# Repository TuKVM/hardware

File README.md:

# TuKVM Hardware

TuKVM is a hardware project that aims to provide a simple but feature rich IP KVM solution. The project is based on the [Tronlong SOM-TLT113](https://www.tronlong.com/Product/show/237.html) SoM, which includes an Allwinner T113-i SoC, with dual-core Cortex-A7 CPU, 256MB DDR3 RAM, and 4GB eMMC.

## Features

* PCIe x1 half-height form factor, with breakable edge connector for mounting in systems without free slots
* HDMI input capture (up to 1080P30) with [MS2109](http://en.macrosilicon.com/info.asp?base_id=2&third_id=50) IC
* ATX power / reset button control with opto-isolator
* Power and HDD LED monitoring with opto-isolator
* 9 pin 2.54mm internal USB OTG port for mass-storage, keyboard, mouse emulation and Ethernet-over-USB
* USB-C external power input and UART console port for debugging
* 100Mbps Ethernet with [LAN8720A](https://www.microchip.com/en-us/product/lan8720a) PHY
* RS232 serial port with 2.54mm header for host system console redirection
* SMBus on PCIe connector for Linux kernel to recongnize the KVM as an IPMI device, using [ipmi_ssif](https://github.com/torvalds/linux/blob/master/drivers/char/ipmi/ipmi_ssif.c) driver
* (Optional) Isolated 802.3af PoE input with [DP1435-5V](https://item.szlcsc.com/6245786.html) controller module
* (Optional) I2C connector for an OLED status display module.

## Status

This project is currently in the prototyping phase. The hardware design is mostly complete, and the first prototype PCBs have been ordered. 

The firmware and software development isn't started yet, but the plan is to port [kvmd](https://github.com/pikvm/kvmd) from PiKVM project to the Allwinner T113-i SoC. Support for SMBus and IPMI protocol will need extra driver and software development. Any help is welcome!

## License

This project is licensed under the CERN Open Hardware License v2 - Permissive license. See the [LICENSE](LICENSE) file for details.

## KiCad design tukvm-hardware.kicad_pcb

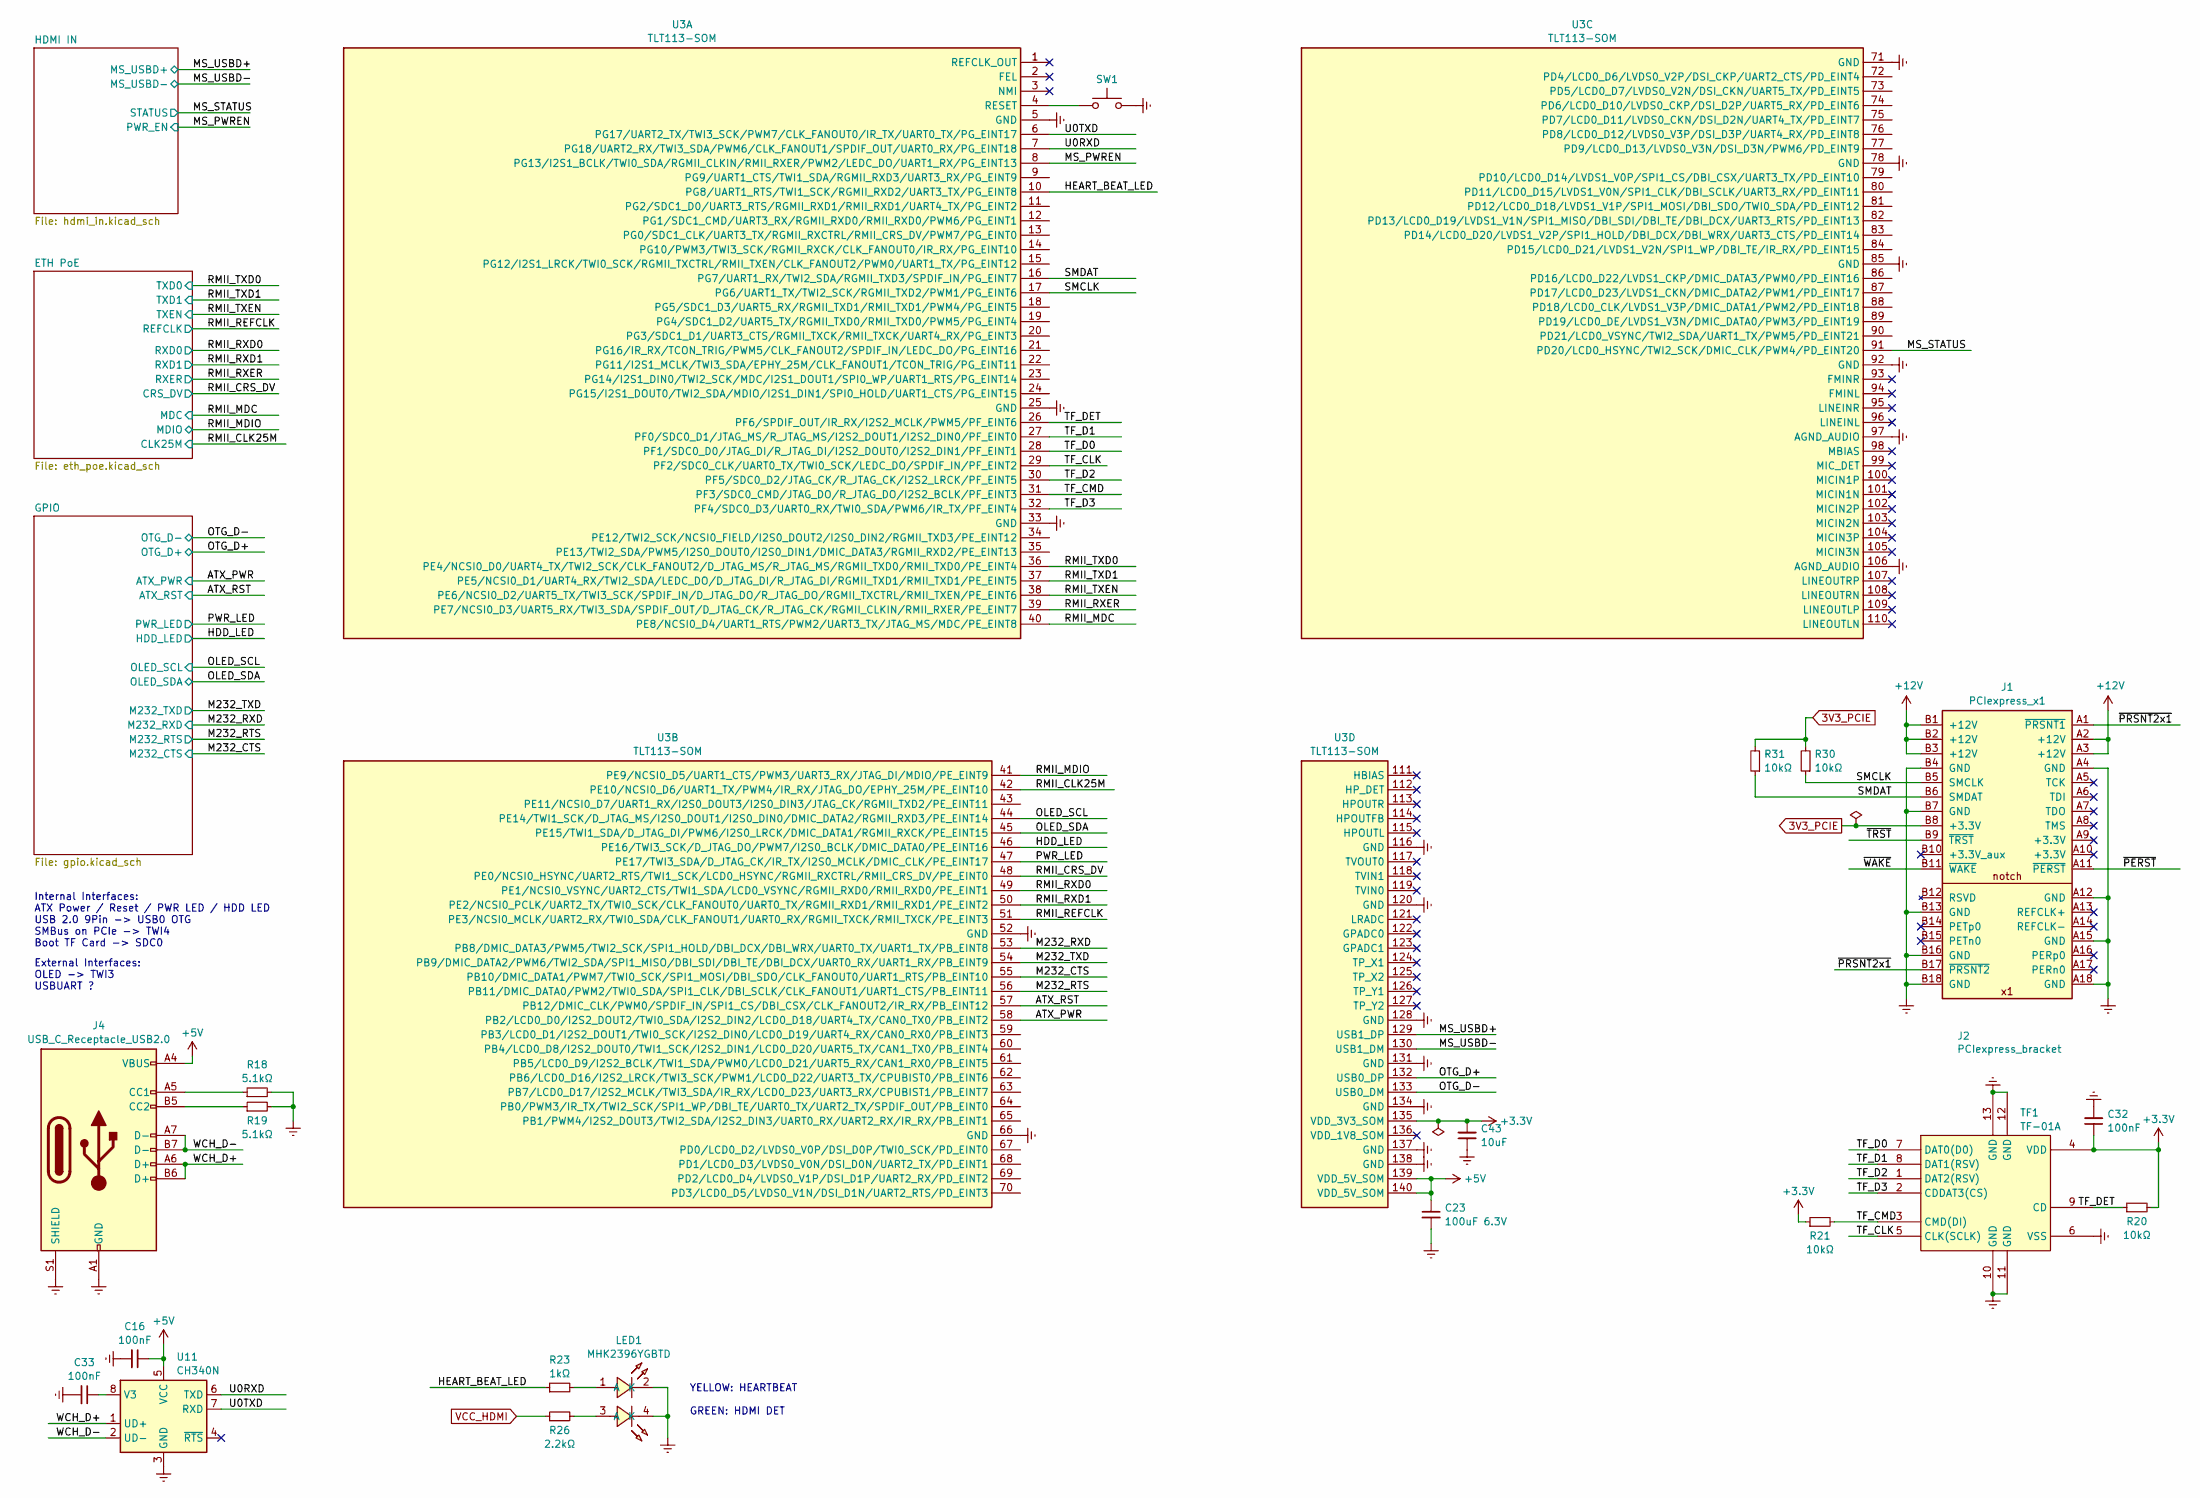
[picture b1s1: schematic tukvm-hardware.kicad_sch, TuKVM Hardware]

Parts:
C16, C32, C33: 100nF; C_0402_1005Metric
C23: 100uF 6.3V; C_1206_3216Metric
C43: 10uF; C_0603_1608Metric
J1: PCIexpress_x1
J2: PCIexpress_bracket; PCIexpress_bracket_low
J4: USB_C_Receptacle_USB2.0; USB-C-TH_TYPE-C-31-M-18
LED1: MHK2396YGBTD; LED-TH_MHK2396YGBTD; LCSC Part C2764899
R18, R19: 5.1kΩ; R_0402_1005Metric
R20, R21, R30, R31: 10kΩ; R_0402_1005Metric
R23: 1kΩ; R_0402_1005Metric
R26: 2.2kΩ; R_0402_1005Metric
SW1: SKRK; SW_Push_SPST_NO_Alps_SKRK
TF1: TF-01A; TF-SMD_TF-01A; LCSC Part C91145
U3: TLT113-SOM; SMD_140P_35X45_SOM_TLT113_PackageLength
U11: CH340N; SOP-8_3.9x4.9mm_P1.27mm

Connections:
3V3_PCIE: J1.B8 (+3.3V), R30.2, R31.2
+3.3V: C32.1, C43.2, R20.2, R21.1, TF1.4 (VDD), U3.135 (VDD_3V3_SOM); also elsewhere on the board
+5V: C16.1, C23.1, J4.A4 (VBUS), J4.A9 (VBUS), J4.B4 (VBUS), J4.B9 (VBUS), U3.139 (VDD_5V_SOM), U3.140 (VDD_5V_SOM), U11.5 (VCC); also elsewhere on the board
+12V: J1.A2 (+12V), J1.A3 (+12V), J1.B1 (+12V), J1.B2 (+12V), J1.B3 (+12V)
/ATX_PWR: U3.58 (PB2/LCD0_D0/I2S2_DOUT2/TWI0_SDA/I2S2_DI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); also elsewhere on the board
/ATX_RST: U3.57 (PB12/DMIC_CLK/PWM0/SPDIF_IN/SPI1_CS/DBI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); also elsewhere on the board
/HDD_LED: U3.46 (PE16/TWI3_SCK/D_JTAG_DO/PWM7/I2S0_BCLK/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); also elsewhere on the board
/HEART_BEAT_LED: R23.1, U3.10 (PG8/UART1_RTS/TWI1_SCK/RGMII_RXD2/UART3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)
/M232_CTS: U3.55 (PB10/DMIC_DATA1/PWM7/TWI0_SCK/SPI1_MOSI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); also elsewhere on the board
/M232_RTS: U3.56 (PB11/DMIC_DATA0/PWM2/TWI0_SDA/SPI1_CLK/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); also elsewhere on the board
/M232_RXD: U3.53 (PB8/DMIC_DATA3/PWM5/TWI2_SCK/SPI1_HOLD/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); also elsewhere on the board
/M232_TXD: U3.54 (PB9/DMIC_DATA2/PWM6/TWI2_SDA/SPI1_MISO/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); also elsewhere on the board
/MS_PWREN: U3.8 (PG13/I2S1_BCLK/TWI0_SDA/RGMII_CLKIN/RMI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); also elsewhere on the board
/MS_STATUS: U3.91 (PD20/LCD0_HSYNC/TWI2_SCK/DMIC_CLK/PWM4/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); also elsewhere on the board
/MS_USBD+: U3.129 (USB1_DP); also elsewhere on the board
/MS_USBD-: U3.130 (USB1_DM); also elsewhere on the board
/OLED_SCL: U3.44 (PE14/TWI1_SCK/D_JTAG_MS/I2S0_DOUT1/I2S0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); also elsewhere on the board
/OLED_SDA: U3.45 (PE15/TWI1_SDA/D_JTAG_DI/PWM6/I2S0_LRCK/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); also elsewhere on the board
/OTG_D+: U3.132 (USB0_DP); also elsewhere on the board
/OTG_D-: U3.133 (USB0_DM); also elsewhere on the board
/PWR_LED: U3.47 (PE17/TWI3_SDA/D_JTAG_CK/IR_TX/I2S0_MCLK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); also elsewhere on the board
/RMII_CLK25M: U3.42 (PE10/NCSI0_D6/UART1_TX/PWM4/IR_RX/JTAG_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); also elsewhere on the board
/RMII_CRS_DV: U3.48 (PE0/NCSI0_HSYNC/UART2_RTS/TWI1_SCK/LCD0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); also elsewhere on the board
/RMII_MDC: U3.40 (PE8/NCSI0_D4/UART1_RTS/PWM2/UART3_TX/JT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); also elsewhere on the board
/RMII_MDIO: U3.41 (PE9/NCSI0_D5/UART1_CTS/PWM3/UART3_RX/JT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); also elsewhere on the board
/RMII_REFCLK: U3.51 (PE3/NCSI0_MCLK/UART2_RX/TWI0_SDA/CLK_FA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); also elsewhere on the board
/RMII_RXD0: U3.49 (PE1/NCSI0_VSYNC/UART2_CTS/TWI1_SDA/LCD0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); also elsewhere on the board
/RMII_RXD1: U3.50 (PE2/NCSI0_PCLK/UART2_TX/TWI0_SCK/CLK_FA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); also elsewhere on the board
/RMII_RXER: U3.39 (PE7/NCSI0_D3/UART5_RX/TWI3_SDA/SPDIF_OU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); also elsewhere on the board
/RMII_TXD0: U3.36 (PE4/NCSI0_D0/UART4_TX/TWI2_SCK/CLK_FANO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); also elsewhere on the board
/RMII_TXD1: U3.37 (PE5/NCSI0_D1/UART4_RX/TWI2_SDA/LEDC_DO/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); also elsewhere on the board
/RMII_TXEN: U3.38 (PE6/NCSI0_D2/UART5_TX/TWI3_SCK/SPDIF_IN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); also elsewhere on the board
/SMCLK: J1.B5 (SMCLK), R30.1, U3.17 (PG6/UART1_TX/TWI2_SCK/RGMII_TXD2/PWM1/P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)
/SMDAT: J1.B6 (SMDAT), R31.1, U3.16 (PG7/UART1_RX/TWI2_SDA/RGMII_TXD3/SPDIF_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)
/TF_CLK: TF1.5 (CLK(SCLK)), U3.29 (PF2/SDC0_CLK/UART0_TX/TWI0_SCK/LEDC_DO/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)
/TF_CMD: R21.2, TF1.3 (CMD(DI)), U3.31 (PF3/SDC0_CMD/JTAG_DO/R_JTAG_DO/I2S2_BCL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)
/TF_D0: TF1.7 (DAT0(D0)), U3.28 (PF1/SDC0_D0/JTAG_DI/R_JTAG_DI/I2S2_DOUT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)
/TF_D1: TF1.8 (DAT1(RSV)), U3.27 (PF0/SDC0_D1/JTAG_MS/R_JTAG_MS/I2S2_DOUT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)
/TF_D2: TF1.1 (DAT2(RSV)), U3.30 (PF5/SDC0_D2/JTAG_CK/R_JTAG_CK/I2S2_LRCK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)
/TF_D3: TF1.2 (CDDAT3(CS)), U3.32 (PF4/SDC0_D3/UART0_RX/TWI0_SDA/PWM6/IR_T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)
/TF_DET: R20.1, TF1.9 (CD), U3.26 (PF6/SPDIF_OUT/IR_RX/I2S2_MCLK/PWM5/PF_E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)
/U0RXD: U3.7 (PG18/UART2_RX/TWI3_SDA/PWM6/CLK_FANOUT1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), U11.6 (TXD)
/U0TXD: U3.6 (PG17/UART2_TX/TWI3_SCK/PWM7/CLK_FANOUT0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), U11.7 (RXD)
/WCH_D+: J4.A6 (D+), J4.B6 (D+), U11.1 (UD+)
/WCH_D-: J4.A7 (D-), J4.B7 (D-), U11.2 (UD-)
/~PERST: J1.A11 (~PERST)
/~PRSNT2x1: J1.A1 (~PRSNT1), J1.B17 (~PRSNT2)
/~TRST: J1.B9 (~TRST)
/~WAKE: J1.B11 (~WAKE)
Earth: C16.2, C23.2, C32.2, C33.2, C43.1, J1.A4 (GND), J1.A12 (GND), J1.A15 (GND), J1.A18 (GND), J1.B4 (GND), J1.B7 (GND), J1.B13 (GND), J1.B16 (GND), J1.B18 (GND), J4.A1 (GND), J4.A12 (GND), J4.B1 (GND), J4.B12 (GND), J4.S1 (SHIELD), LED1.2 (K), LED1.4 (K), R18.2, R19.2, SW1.2, TF1.6 (VSS), TF1.10 (GND), TF1.11 (GND), TF1.12 (GND), TF1.13 (GND), U3.5 (GND), U3.25 (GND), U3.33 (GND), U3.52 (GND), U3.66 (GND), U3.71 (GND), U3.78 (GND), U3.85 (GND), U3.92 (GND), U3.97 (AGND_AUDIO), U3.106 (AGND_AUDIO), U3.116 (GND), U3.120 (GND), U3.128 (GND), U3.131 (GND), U3.134 (GND), U3.137 (GND), U3.138 (GND), U11.3 (GND); also elsewhere on the board
unnamed: J4.A5 (CC1), R18.1
unnamed: J4.B5 (CC2), R19.1
unnamed: LED1.1 (A), R23.2
unnamed: LED1.3 (A), R26.2
unnamed: SW1.1, U3.4 (RESET)
unnamed: C33.1, U11.8 (V3)
VCC_HDMI: R26.1; also elsewhere on the board

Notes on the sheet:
External Interfaces: OLED -> TWI3 USBUART ?
YELLOW: HEARTBEAT GREEN: HDMI DET
Internal Interfaces: ATX Power / Reset / PWR LED / HDD LED USB 2.0 9Pin -> USB0 OTG SMBus on PCIe -> TWI4 Boot TF Card -> SDC0

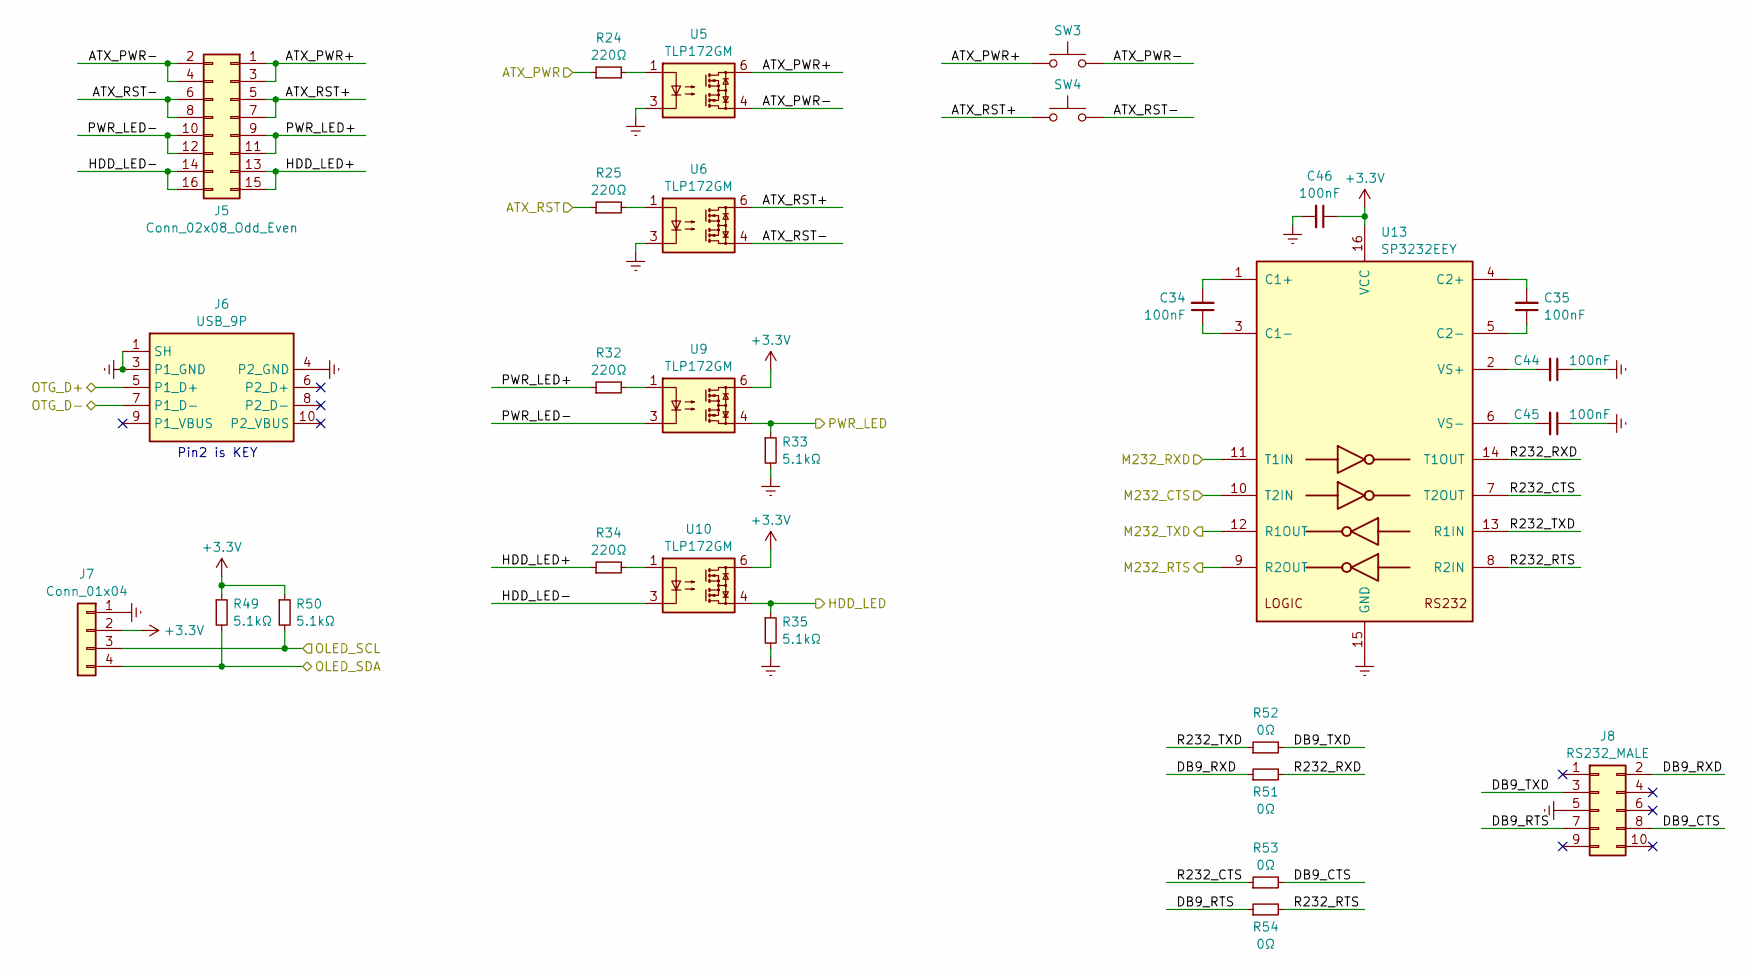
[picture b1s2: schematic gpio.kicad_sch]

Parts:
C34, C35, C44, C45, C46: 100nF; C_0402_1005Metric
J5: Conn_02x08_Odd_Even; PinHeader_2x08_P2.54mm_Horizontal
J6: USB_9P; USB_9P_P2.54mm_Horizontal
J7: Conn_01x04; PinHeader_1x04_P2.54mm_Horizontal
J8: RS232_MALE; IDC-SMD_10P-P2.54-V-R2-C5-S9.50
R24, R25, R32, R34: 220Ω; R_0402_1005Metric
R33, R35, R49, R50: 5.1kΩ; R_0402_1005Metric
R51, R52, R53, R54: 0Ω; R_0402_1005Metric
SW3, SW4: TS-1187A; SW_Push_1P1T_XKB_TS-1187A
U5, U6, U9, U10: TLP172GM; MFSOP6-4_4.4x3.6mm_P1.27mm; LCSC Part C261926
U13: SP3232EEY; TSSOP-16_4.4x5mm_P0.65mm; LCSC Part C13482

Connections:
+3.3V: C46.1, J7.2, R49.1, R50.1, U9.6, U10.6, U13.16 (VCC); also elsewhere on the board
/ATX_PWR: R24.1; also elsewhere on the board
/ATX_RST: R25.1; also elsewhere on the board
/GPIO/ATX_PWR+: J5.1, J5.3, SW3.1, U5.6
/GPIO/ATX_PWR-: J5.2, J5.4, SW3.2, U5.4
/GPIO/ATX_RST+: J5.5, J5.7, SW4.1, U6.6
/GPIO/ATX_RST-: J5.6, J5.8, SW4.2, U6.4
/GPIO/DB9_CTS: J8.8, R53.2
/GPIO/DB9_RTS: J8.7, R54.1
/GPIO/DB9_RXD: J8.2, R51.1
/GPIO/DB9_TXD: J8.3, R52.2
/GPIO/HDD_LED+: J5.13, J5.15, R34.1
/GPIO/HDD_LED-: J5.14, J5.16, U10.3
/GPIO/PWR_LED+: J5.9, J5.11, R32.1
/GPIO/PWR_LED-: J5.10, J5.12, U9.3
/GPIO/R232_CTS: R53.1, U13.7 (T2OUT)
/GPIO/R232_RTS: R54.2, U13.8 (R2IN)
/GPIO/R232_RXD: R51.2, U13.14 (T1OUT)
/GPIO/R232_TXD: R52.1, U13.13 (R1IN)
/HDD_LED: R35.1, U10.4; also elsewhere on the board
/M232_CTS: U13.10 (T2IN); also elsewhere on the board
/M232_RTS: U13.9 (R2OUT); also elsewhere on the board
/M232_RXD: U13.11 (T1IN); also elsewhere on the board
/M232_TXD: U13.12 (R1OUT); also elsewhere on the board
/OLED_SCL: J7.3, R50.2; also elsewhere on the board
/OLED_SDA: J7.4, R49.2; also elsewhere on the board
/OTG_D+: J6.5 (P1_D+); also elsewhere on the board
/OTG_D-: J6.7 (P1_D-); also elsewhere on the board
/PWR_LED: R33.1, U9.4; also elsewhere on the board
Earth: C44.1, C45.1, C46.2, J6.1 (SH), J6.3 (P1_GND), J6.4 (P2_GND), J7.1, J8.5, R33.2, R35.2, U5.3, U6.3, U13.15 (GND); also elsewhere on the board
unnamed: R24.2, U5.1
unnamed: R25.2, U6.1
unnamed: R32.2, U9.1
unnamed: R34.2, U10.1
unnamed: C34.2, U13.1 (C1+)
unnamed: C34.1, U13.3 (C1-)
unnamed: C35.2, U13.4 (C2+)
unnamed: C35.1, U13.5 (C2-)
unnamed: C44.2, U13.2 (VS+)
unnamed: C45.2, U13.6 (VS-)

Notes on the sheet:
Pin2 is KEY

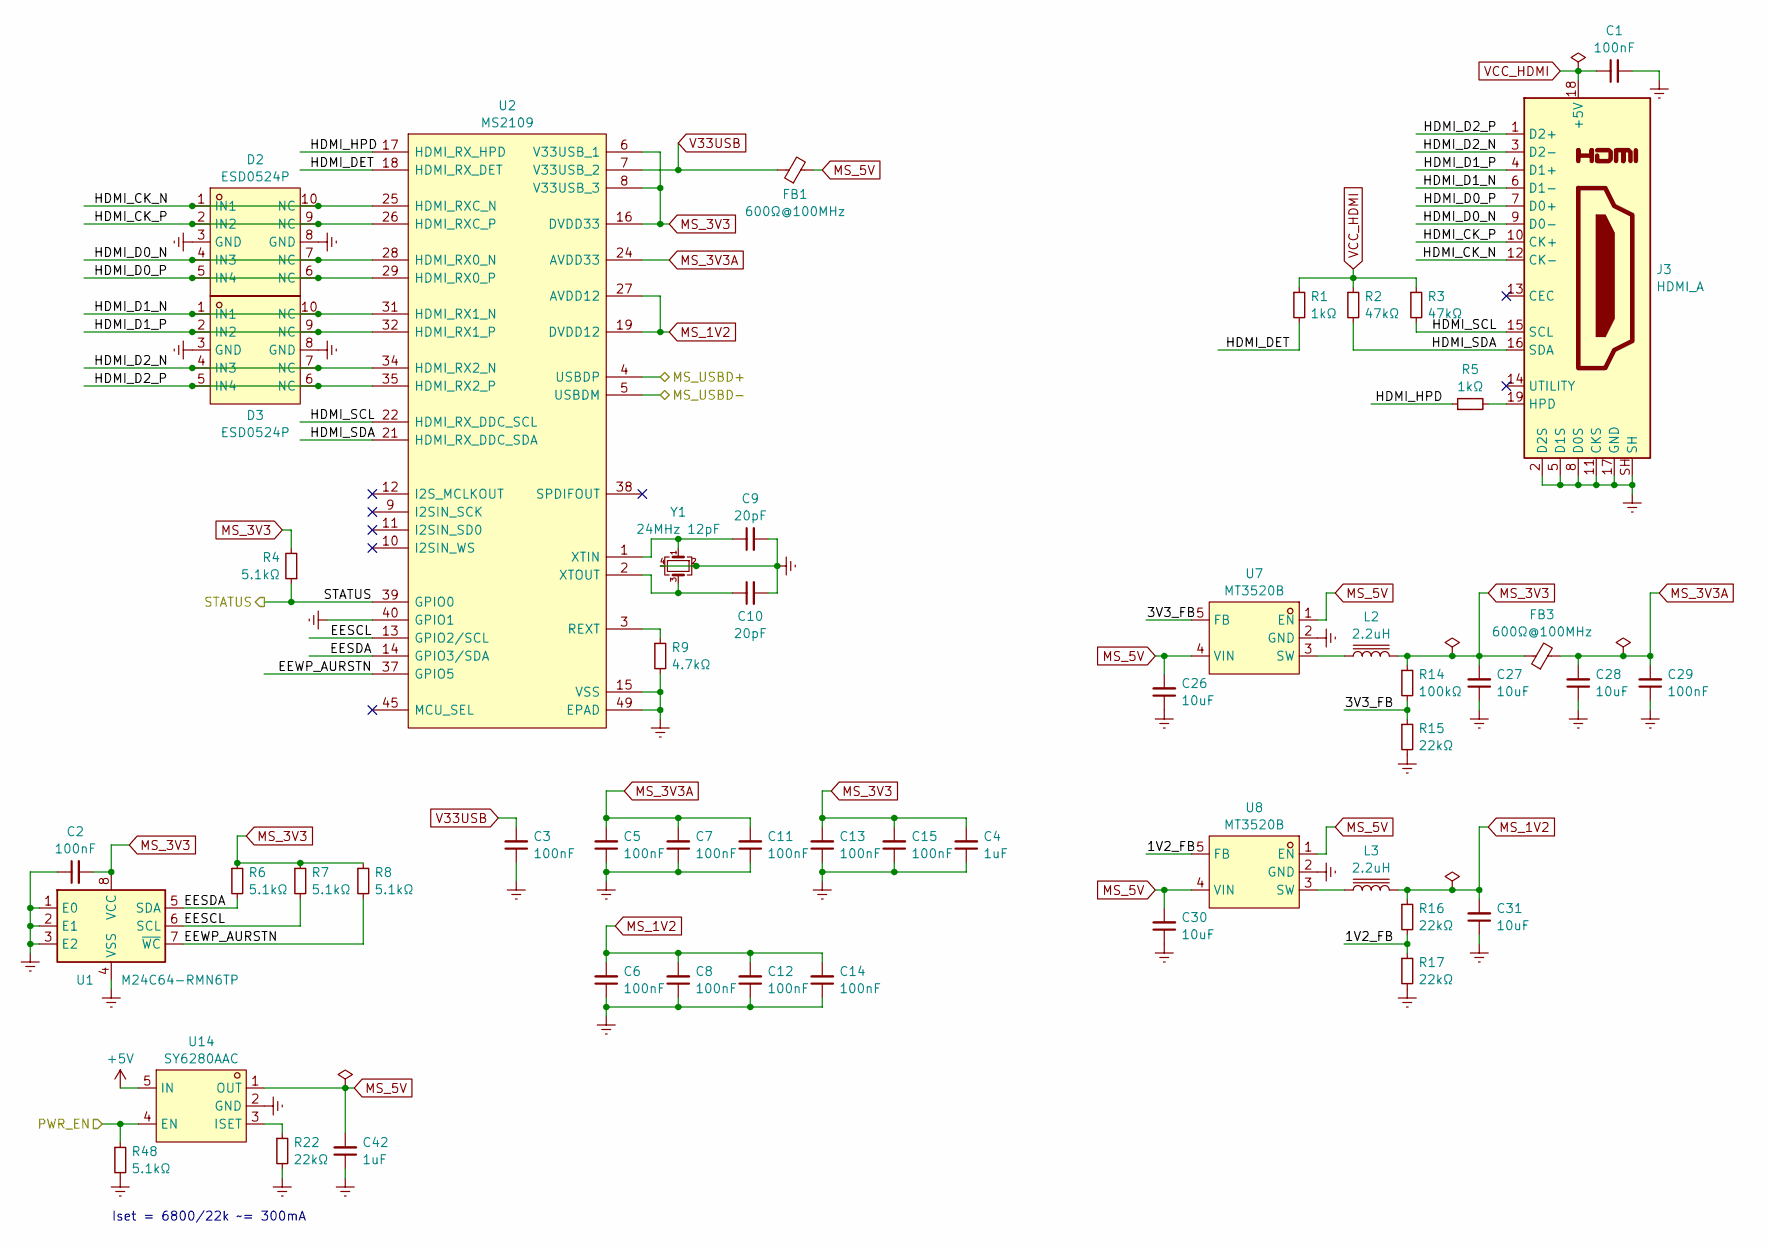
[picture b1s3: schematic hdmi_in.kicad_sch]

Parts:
C1, C2, C3, C5, C6, C7, C8, C11, C12, C13, C14, C15, C29: 100nF; C_0402_1005Metric
C4, C42: 1uF; C_0402_1005Metric
C9, C10: 20pF; C_0402_1005Metric
C26, C27, C28, C30, C31: 10uF; C_0603_1608Metric
D2, D3: ESD0524P; DFN-10_L2.5-W1.0-P0.50-BL; LCSC Part C484320
FB1, FB3: 600Ω@100MHz; L_0603_1608Metric; LCSC Part C1002
J3: HDMI_A; HDMI_A_Molex_208658-1001_Horizontal
L2, L3: 2.2uH; L_Cenker_CKCS201610; LCSC Part C354533
R1, R5: 1kΩ; R_0402_1005Metric
R2, R3: 47kΩ; R_0402_1005Metric
R4, R6, R7, R8, R48: 5.1kΩ; R_0402_1005Metric
R9: 4.7kΩ; R_0402_1005Metric
R14: 100kΩ; R_0402_1005Metric
R15, R16, R17, R22: 22kΩ; R_0402_1005Metric
U1: M24C64-RMN6TP; SOIC-8_3.9x4.9mm_P1.27mm; LCSC Part C79988
U2: MS2109; QFN-48-1EP_7x7mm_P0.5mm_EP5.1x5.1mm
U7, U8: MT3520B; SOT-23-5; LCSC Part C2684933
U14: SY6280AAC; SOT-23-5; LCSC Part C55136
Y1: 24MHz 12pF; Crystal_SMD_3225-4Pin_3.2x2.5mm; LCSC Part C271629

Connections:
+5V: U14.5 (IN); also elsewhere on the board
/HDMI IN/1V2_FB: R16.2, R17.1, U8.5 (FB)
/HDMI IN/3V3_FB: R14.2, R15.1, U7.5 (FB)
/HDMI IN/EESCL: R7.2, U1.6 (SCL), U2.13 (GPIO2/SCL)
/HDMI IN/EESDA: R6.2, U1.5 (SDA), U2.14 (GPIO3/SDA)
/HDMI IN/EEWP_AURSTN: R8.2, U1.7 (~WC), U2.37 (GPIO5)
/HDMI IN/HDMI_CK_N: D2.1 (IN1), D2.10 (NC), J3.12 (CK-), U2.25 (HDMI_RXC_N)
/HDMI IN/HDMI_CK_P: D2.2 (IN2), D2.9 (NC), J3.10 (CK+), U2.26 (HDMI_RXC_P)
/HDMI IN/HDMI_D0_N: D2.4 (IN3), D2.7 (NC), J3.9 (D0-), U2.28 (HDMI_RX0_N)
/HDMI IN/HDMI_D0_P: D2.5 (IN4), D2.6 (NC), J3.7 (D0+), U2.29 (HDMI_RX0_P)
/HDMI IN/HDMI_D1_N: D3.1 (IN1), D3.10 (NC), J3.6 (D1-), U2.31 (HDMI_RX1_N)
/HDMI IN/HDMI_D1_P: D3.2 (IN2), D3.9 (NC), J3.4 (D1+), U2.32 (HDMI_RX1_P)
/HDMI IN/HDMI_D2_N: D3.4 (IN3), D3.7 (NC), J3.3 (D2-), U2.34 (HDMI_RX2_N)
/HDMI IN/HDMI_D2_P: D3.5 (IN4), D3.6 (NC), J3.1 (D2+), U2.35 (HDMI_RX2_P)
/HDMI IN/HDMI_DET: R1.2, U2.18 (HDMI_RX_DET)
/HDMI IN/HDMI_HPD: R5.1, U2.17 (HDMI_RX_HPD)
/HDMI IN/HDMI_SCL: J3.15 (SCL), R3.2, U2.22 (HDMI_RX_DDC_SCL)
/HDMI IN/HDMI_SDA: J3.16 (SDA), R2.2, U2.21 (HDMI_RX_DDC_SDA)
/MS_PWREN: R48.1, U14.4 (EN); also elsewhere on the board
/MS_STATUS: R4.1, U2.39 (GPIO0); also elsewhere on the board
/MS_USBD+: U2.4 (USBDP); also elsewhere on the board
/MS_USBD-: U2.5 (USBDM); also elsewhere on the board
Earth: C1.2, C2.1, C3.1, C4.1, C5.1, C6.1, C7.1, C8.1, C9.2, C10.2, C11.1, C12.1, C13.1, C14.1, C15.1, C26.1, C27.1, C28.1, C29.1, C30.1, C31.1, C42.1, D2.3 (GND), D2.8 (GND), D3.3 (GND), D3.8 (GND), J3.2 (D2S), J3.5 (D1S), J3.8 (D0S), J3.11 (CKS), J3.17 (GND), J3.SH, R9.2, R15.2, R17.2, R22.2, R48.2, U1.1 (E0), U1.2 (E1), U1.3 (E2), U1.4 (VSS), U2.15 (VSS), U2.20 (VSS), U2.36 (VSS), U2.40 (GPIO1), U2.42 (VSS), U2.43 (VSS), U2.46 (VSS), U2.48 (VSS), U2.49 (EPAD), U7.2 (GND), U8.2 (GND), U14.2 (GND), Y1.2, Y1.4; also elsewhere on the board
MS_1V2: C6.2, C8.2, C12.2, C14.2, C31.2, L3.2, R16.1, U2.19 (DVDD12), U2.27 (AVDD12), U2.33 (AVDD12), U2.41 (DVDD12)
MS_3V3: C2.2, C4.2, C13.2, C15.2, C27.2, FB3.1, L2.2, R4.2, R6.1, R7.1, R8.1, R14.1, U1.8 (VCC), U2.6 (V33USB_1), U2.8 (V33USB_3), U2.16 (DVDD33), U2.23 (DVDD33), U2.44 (DVDD33)
MS_3V3A: C5.2, C7.2, C11.2, C28.2, C29.2, FB3.2, U2.24 (AVDD33), U2.30 (AVDD33), U2.47 (AVDD33)
MS_5V: C26.2, C30.2, C42.2, FB1.2, U7.1 (EN), U7.4 (VIN), U8.1 (EN), U8.4 (VIN), U14.1 (OUT)
unnamed: J3.19 (HPD), R5.2
unnamed: R9.1, U2.3 (REXT)
unnamed: C9.1, U2.1 (XTIN), Y1.1
unnamed: C10.1, U2.2 (XTOUT), Y1.3
unnamed: L2.1, U7.3 (SW)
unnamed: L3.1, U8.3 (SW)
unnamed: R22.1, U14.3 (ISET)
V33USB: C3.2, FB1.1, U2.7 (V33USB_2)
VCC_HDMI: C1.1, J3.18 (+5V), R1.1, R2.1, R3.1; also elsewhere on the board

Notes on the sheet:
Iset = 6800/22k ~= 300mA

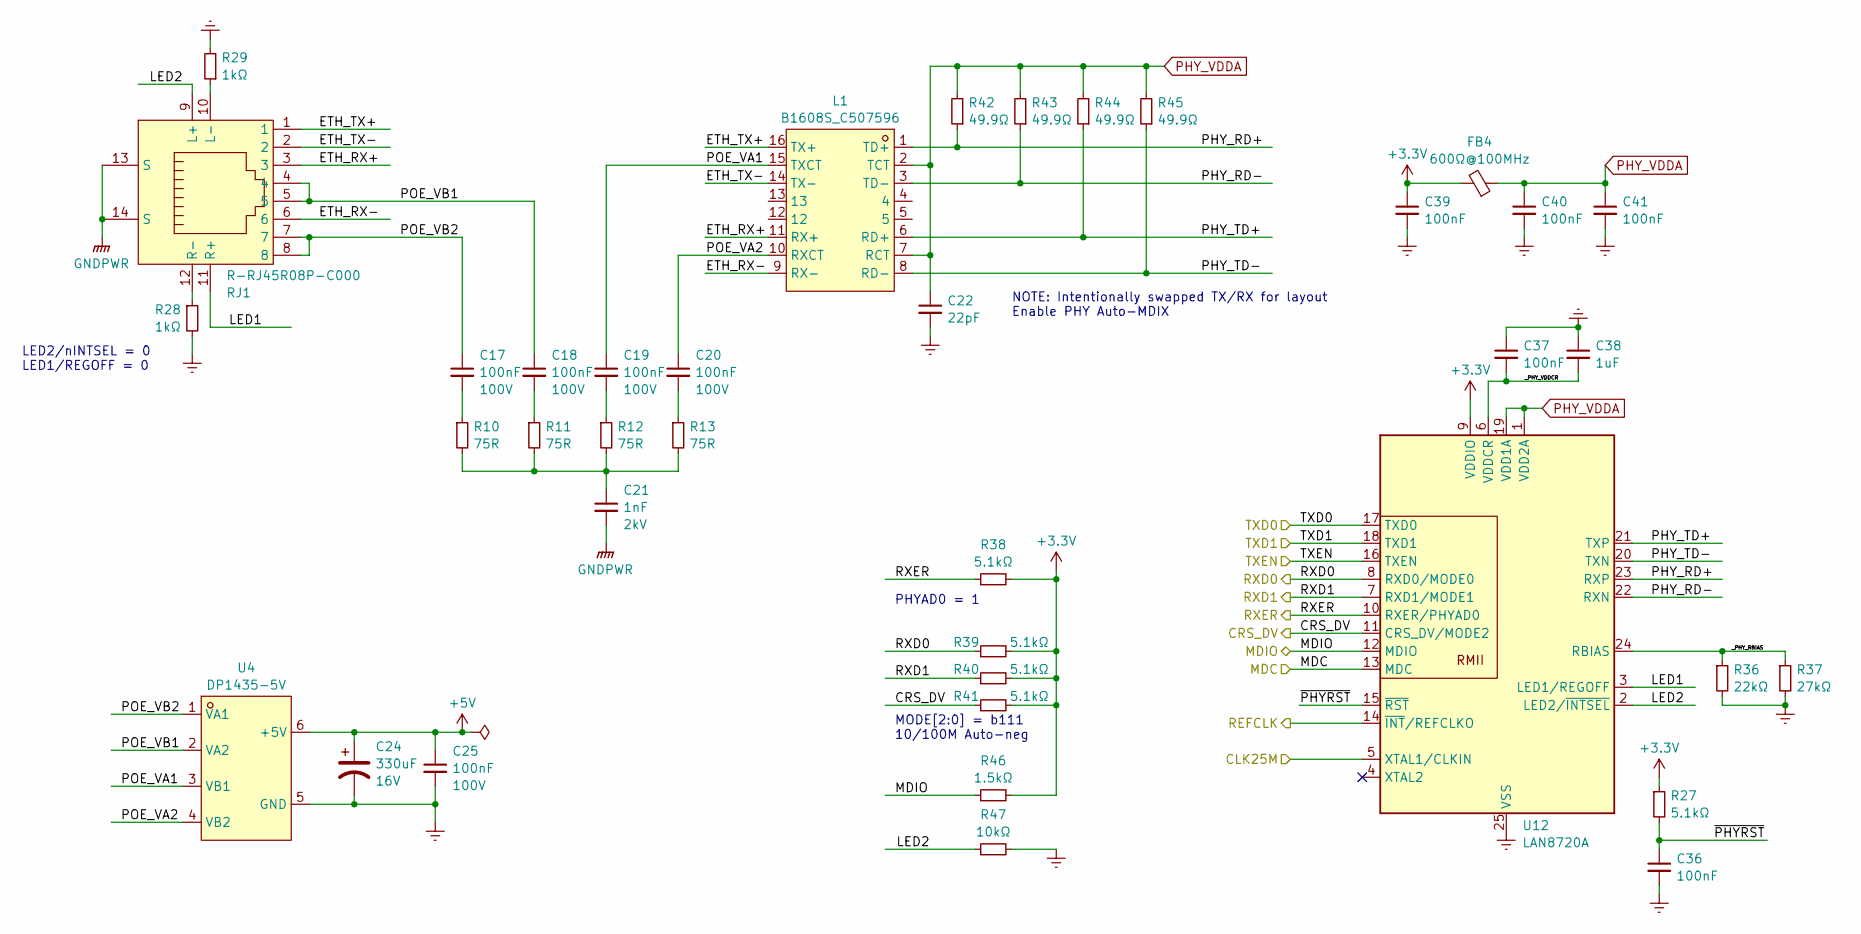
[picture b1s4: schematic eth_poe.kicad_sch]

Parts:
C17, C18, C19, C20, C25: 100nF; C_0805_2012Metric; Voltage 100V
C21: 1nF; C_1206_3216Metric; Voltage 2kV
C22: 22pF; C_0402_1005Metric
C24: 330uF; C_Elec_6.3x7.7; Voltage 16V
C36, C37, C39, C40, C41: 100nF; C_0402_1005Metric
C38: 1uF; C_0402_1005Metric
FB4: 600Ω@100MHz; L_0603_1608Metric; LCSC Part C1002
L1: B1608S_C507596; SMD-16_L12.7-W7.0-P1.27-LS9.5-BL; LCSC Part C507596
R10, R11, R12, R13: 75R; R_0603_1608Metric
R27, R38, R39, R40, R41: 5.1kΩ; R_0402_1005Metric
R28, R29: 1kΩ; R_0402_1005Metric
R36: 22kΩ; R_0402_1005Metric
R37: 27kΩ; R_0603_1608Metric
R42, R43, R44, R45: 49.9Ω; R_0402_1005Metric
R46: 1.5kΩ; R_0402_1005Metric
R47: 10kΩ; R_0402_1005Metric
RJ1: R-RJ45R08P-C000; RJ45-TH_R-RJ45R08P-C000; LCSC Part C386757
U4: DP1435-5V; PWRM-TH_DP1435-XX; LCSC Part C5380097
U12: LAN8720A; VQFN-24-1EP_4x4mm_P0.5mm_EP2.5x2.5mm

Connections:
+3.3V: C39.1, FB4.2, R27.1, R38.2, R39.2, R40.2, R41.2, R46.2, U12.9 (VDDIO); also elsewhere on the board
+5V: C24.1, C25.1, U4.6 (+5V); also elsewhere on the board
/ETH PoE/ETH_RX+: L1.11 (RX+), RJ1.3
/ETH PoE/ETH_RX-: L1.9 (RX-), RJ1.6
/ETH PoE/ETH_TX+: L1.16 (TX+), RJ1.1
/ETH PoE/ETH_TX-: L1.14 (TX-), RJ1.2
/ETH PoE/LED1: RJ1.11 (R+), U12.3 (LED1/REGOFF)
/ETH PoE/LED2: R47.1, RJ1.9 (L+), U12.2 (LED2/~INTSEL)
/ETH PoE/PHY_RD+: L1.1 (TD+), R42.1, U12.23 (RXP)
/ETH PoE/PHY_RD-: L1.3 (TD-), R43.1, U12.22 (RXN)
/ETH PoE/PHY_TD+: L1.6 (RD+), R44.1, U12.21 (TXP)
/ETH PoE/PHY_TD-: L1.8 (RD-), R45.1, U12.20 (TXN)
/ETH PoE/POE_VA1: C19.1, L1.15 (TXCT), U4.3 (VB1)
/ETH PoE/POE_VA2: C20.1, L1.10 (RXCT), U4.4 (VB2)
/ETH PoE/POE_VB1: C18.1, RJ1.4, RJ1.5, U4.2 (VA2)
/ETH PoE/POE_VB2: C17.1, RJ1.7, RJ1.8, U4.1 (VA1)
/ETH PoE/_PHY_RBIAS: R36.1, R37.1, U12.24 (RBIAS)
/ETH PoE/_PHY_VDDCR: C37.2, C38.2, U12.6 (VDDCR)
/ETH PoE/~PHYRST: C36.1, R27.2, U12.15 (~RST)
/RMII_CLK25M: U12.5 (XTAL1/CLKIN); also elsewhere on the board
/RMII_CRS_DV: R41.1, U12.11 (CRS_DV/MODE2); also elsewhere on the board
/RMII_MDC: U12.13 (MDC); also elsewhere on the board
/RMII_MDIO: R46.1, U12.12 (MDIO); also elsewhere on the board
/RMII_REFCLK: U12.14 (~INT/REFCLKO); also elsewhere on the board
/RMII_RXD0: R39.1, U12.8 (RXD0/MODE0); also elsewhere on the board
/RMII_RXD1: R40.1, U12.7 (RXD1/MODE1); also elsewhere on the board
/RMII_RXER: R38.1, U12.10 (RXER/PHYAD0); also elsewhere on the board
/RMII_TXD0: U12.17 (TXD0); also elsewhere on the board
/RMII_TXD1: U12.18 (TXD1); also elsewhere on the board
/RMII_TXEN: U12.16 (TXEN); also elsewhere on the board
Earth: C22.2, C24.2, C25.2, C36.2, C37.1, C38.1, C39.2, C40.2, C41.2, R28.2, R29.2, R36.2, R37.2, R47.2, U4.5 (GND), U12.25 (VSS); also elsewhere on the board
GNDPWR: C21.2, RJ1.13 (S), RJ1.14 (S)
unnamed: C17.2, R10.1
unnamed: C18.2, R11.1
unnamed: C19.2, R12.1
unnamed: C20.2, R13.1
unnamed: C21.1, R10.2, R11.2, R12.2, R13.2
unnamed: R29.1, RJ1.10 (L-)
unnamed: R28.1, RJ1.12 (R-)
PHY_VDDA: C22.1, C40.1, C41.1, FB4.1, L1.2 (TCT), L1.7 (RCT), R42.2, R43.2, R44.2, R45.2, U12.1 (VDD2A), U12.19 (VDD1A)

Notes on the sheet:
LED2/nINTSEL = 0 LED1/REGOFF = 0
PHYAD0 = 1
NOTE: Intentionally swapped TX/RX for layout Enable PHY Auto-MDIX
MODE[2:0] = b111 10/100M Auto-neg

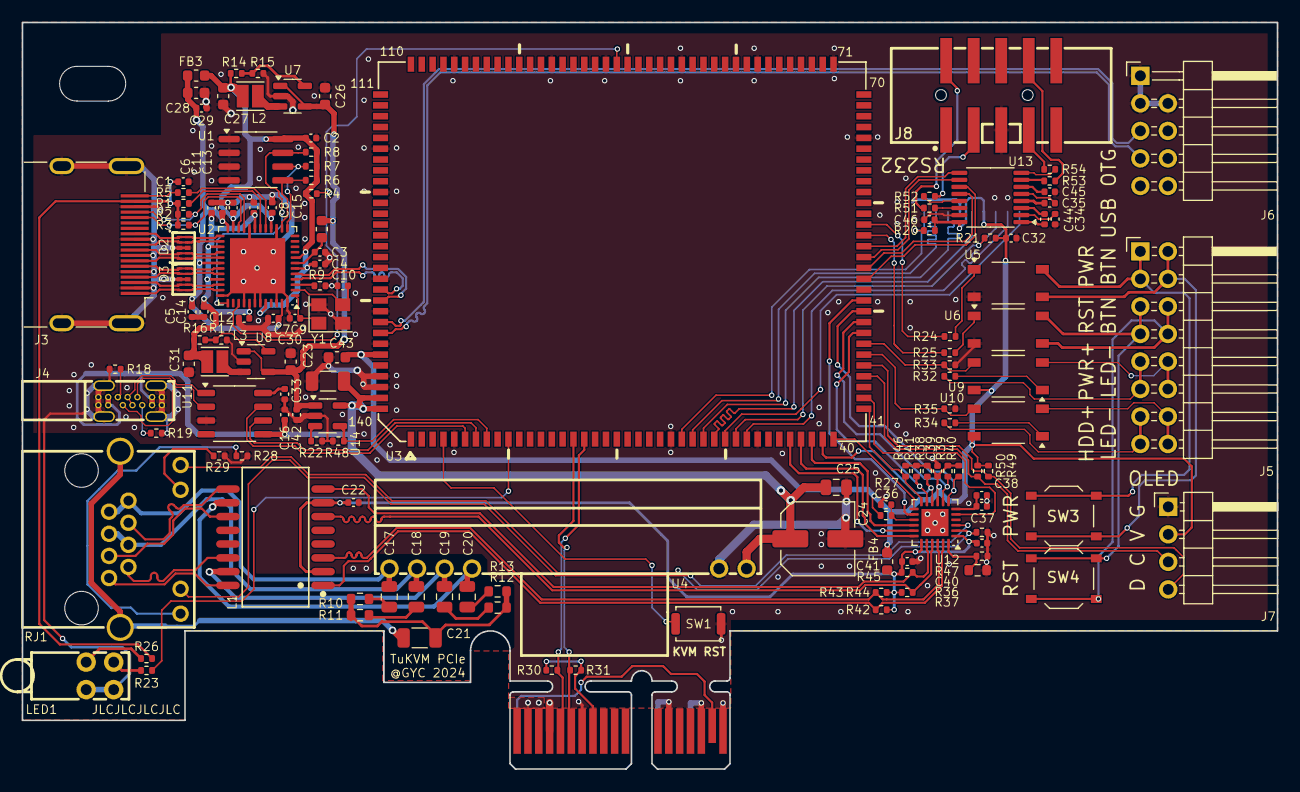
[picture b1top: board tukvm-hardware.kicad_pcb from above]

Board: 2 copper layers, 115.8 x 68.9 mm, 137 parts (1 on the bottom side), 135 nets.

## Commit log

2024-02-25 Add PCI express library
2024-02-25 Add general library
2024-02-25 Add sch & pcb for MCORE-H616 version
2024-02-29 Add Tronglong TLT113 SOM library
2024-02-29 Update pcb & sch for T113 SOM
2024-02-29 Add 3dmodels for some parts
2024-02-29 Add readme and license
2024-03-01 Add oled readme
2024-03-10 Fix MS2109 symbol power pins, initial v1 release
2024-05-07 Fix OTG USB polarity
